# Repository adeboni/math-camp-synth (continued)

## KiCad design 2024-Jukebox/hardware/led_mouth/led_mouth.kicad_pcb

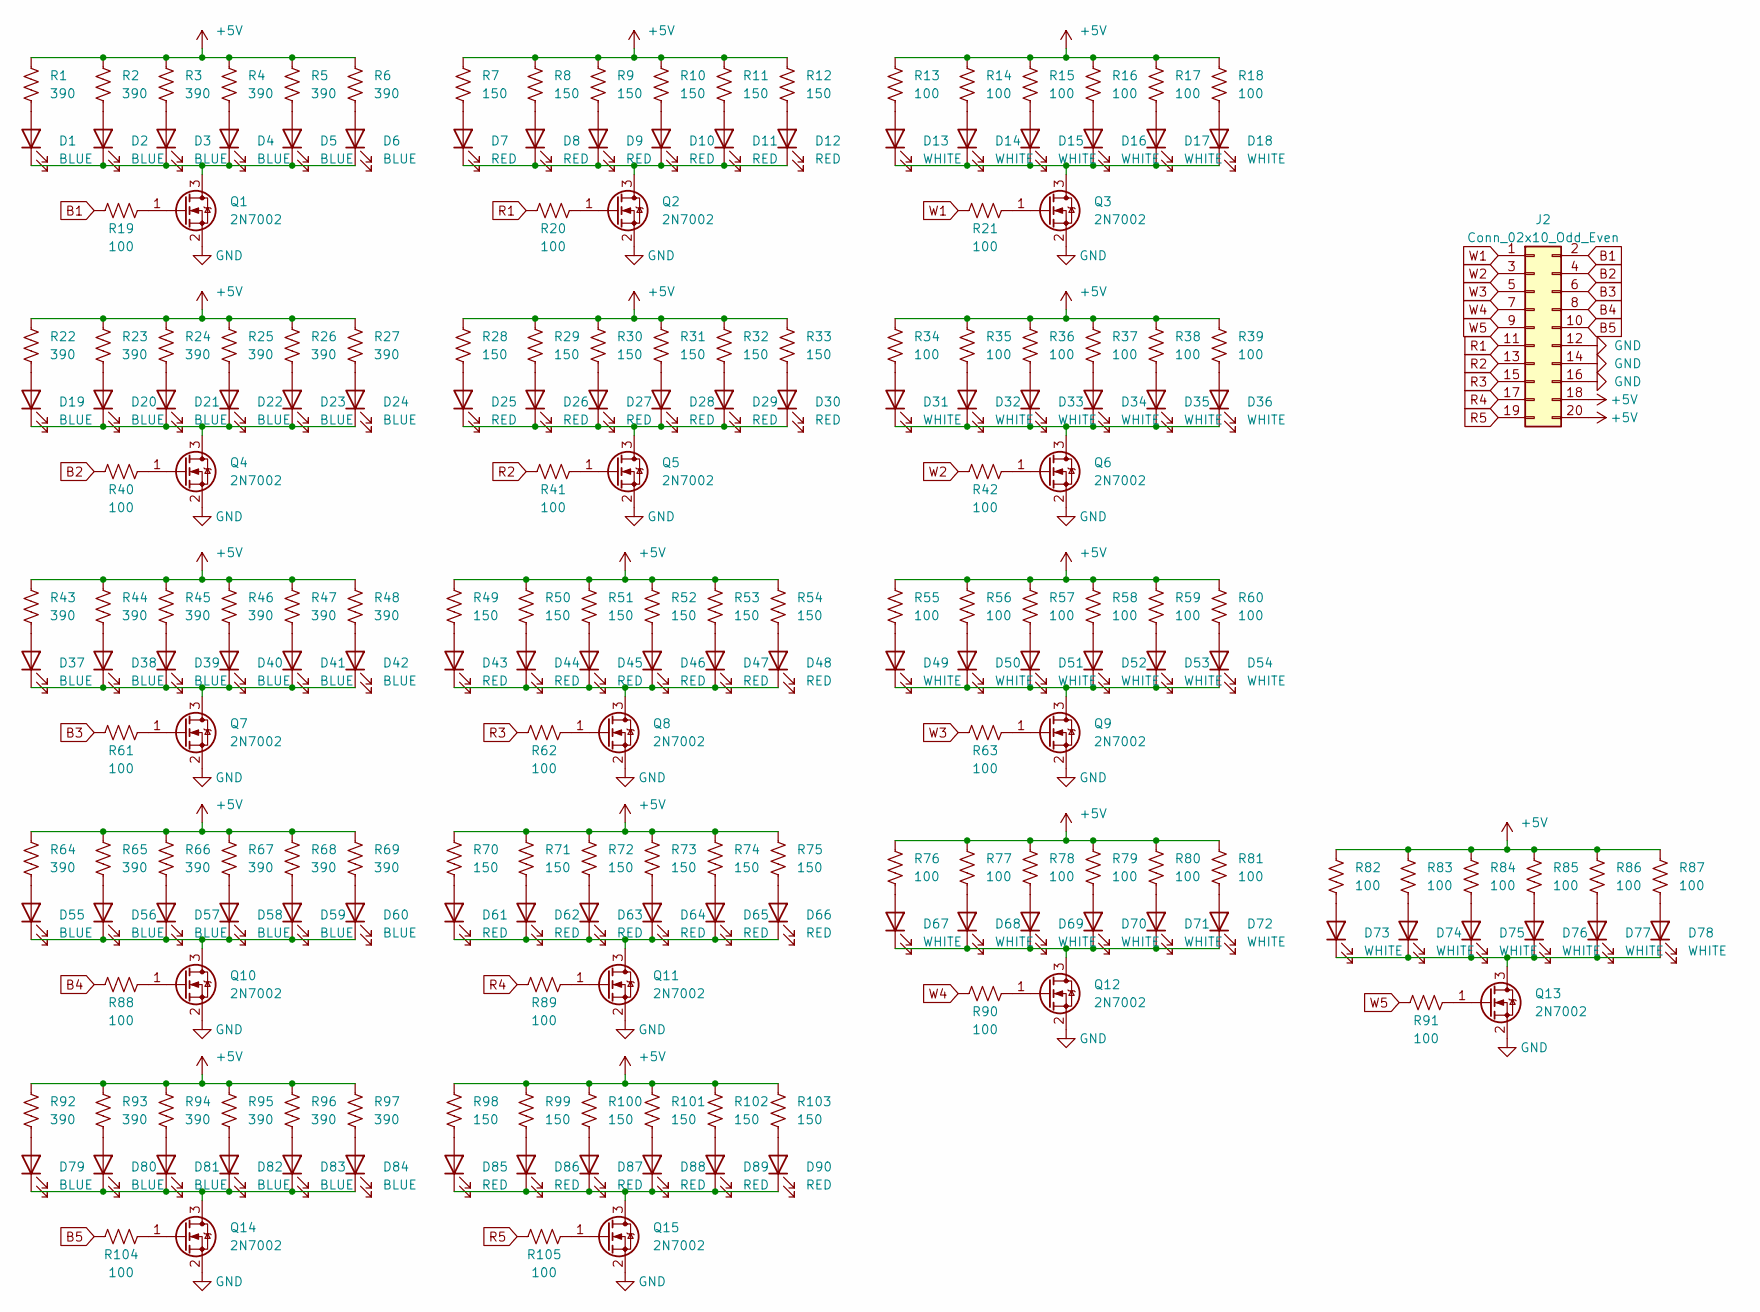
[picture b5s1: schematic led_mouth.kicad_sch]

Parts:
D1, D2, D3, D4, D5, D6, D19, D20, D21, D22, D23, D24, D37, D38, D39, D40, D41, D42, D55, D56, D57, D58, D59, D60, D79, D80, D81, D82, D83, D84: BLUE; LED_0603_1608Metric
D7, D8, D9, D10, D11, D12, D25, D26, D27, D28, D29, D30, D43, D44, D45, D46, D47, D48, D61, D62, D63, D64, D65, D66, D85, D86, D87, D88, D89, D90: RED; LED_0603_1608Metric
D13, D14, D15, D16, D17, D18, D31, D32, D33, D34, D35, D36, D49, D50, D51, D52, D53, D54, D67, D68, D69, D70, D71, D72, D73, D74, D75, D76, D77, D78: WHITE; LED_0603_1608Metric
J2: Conn_02x10_Odd_Even; IDC-Header_2x10_P2.54mm_Vertical_SMD
Q1, Q2, Q3, Q4, Q5, Q6, Q7, Q8, Q9, Q10, Q11, Q12, Q13, Q14, Q15: 2N7002; SOT-23
R1, R2, R3, R4, R5, R6, R22, R23, R24, R25, R26, R27, R43, R44, R45, R46, R47, R48, R64, R65, R66, R67, R68, R69, R92, R93, R94, R95, R96, R97: 390; R_0603_1608Metric
R7, R8, R9, R10, R11, R12, R28, R29, R30, R31, R32, R33, R49, R50, R51, R52, R53, R54, R70, R71, R72, R73, R74, R75, R98, R99, R100, R101, R102, R103: 150; R_0603_1608Metric
R13, R14, R15, R16, R17, R18, R19, R20, R21, R34, R35, R36, R37, R38, R39, R40, R41, R42, R55, R56, R57, R58, R59, R60, R61, R62, R63, R76, R77, R78, R79, R80, R81, R82, R83, R84, R85, R86, R87, R88, R89, R90, R91, R104, R105: 100; R_0603_1608Metric

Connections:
+5V: J2.18, J2.20, R1.2, R2.2, R3.2, R4.2, R5.2, R6.2, R7.2, R8.2, R9.2, R10.2, R11.2, R12.2, R13.2, R14.2, R15.2, R16.2, R17.2, R18.2, R22.2, R23.2, R24.2, R25.2, R26.2, R27.2, R28.2, R29.2, R30.2, R31.2, R32.2, R33.2, R34.2, R35.2, R36.2, R37.2, R38.2, R39.2, R43.2, R44.2, R45.2, R46.2, R47.2, R48.2, R49.2, R50.2, R51.2, R52.2, R53.2, R54.2, R55.2, R56.2, R57.2, R58.2, R59.2, R60.2, R64.2, R65.2, R66.2, R67.2, R68.2, R69.2, R70.2, R71.2, R72.2, R73.2, R74.2, R75.2, R76.2, R77.2, R78.2, R79.2, R80.2, R81.2, R82.2, R83.2, R84.2, R85.2, R86.2, R87.2, R92.2, R93.2, R94.2, R95.2, R96.2, R97.2, R98.2, R99.2, R100.2, R101.2, R102.2, R103.2
B1: J2.2, R19.1
B2: J2.4, R40.1
B3: J2.6, R61.1
B4: J2.8, R88.1
B5: J2.10, R104.1
GND: J2.12, J2.14, J2.16, Q1.2 (S), Q2.2 (S), Q3.2 (S), Q4.2 (S), Q5.2 (S), Q6.2 (S), Q7.2 (S), Q8.2 (S), Q9.2 (S), Q10.2 (S), Q11.2 (S), Q12.2 (S), Q13.2 (S), Q14.2 (S), Q15.2 (S)
unnamed: D1.2 (A), R1.1
unnamed: D1.1 (K), D2.1 (K), D3.1 (K), D4.1 (K), D5.1 (K), D6.1 (K), Q1.3 (D)
unnamed: D2.2 (A), R2.1
unnamed: D3.2 (A), R3.1
unnamed: D4.2 (A), R4.1
unnamed: D5.2 (A), R5.1
unnamed: D6.2 (A), R6.1
unnamed: D7.2 (A), R7.1
unnamed: D8.2 (A), R8.1
unnamed: D9.2 (A), R9.1
unnamed: D10.2 (A), R10.1
unnamed: D7.1 (K), D8.1 (K), D9.1 (K), D10.1 (K), D11.1 (K), D12.1 (K), Q2.3 (D)
unnamed: D11.2 (A), R11.1
unnamed: D12.2 (A), R12.1
unnamed: D13.2 (A), R13.1
unnamed: D13.1 (K), D14.1 (K), D15.1 (K), D16.1 (K), D17.1 (K), D18.1 (K), Q3.3 (D)
unnamed: D14.2 (A), R14.1
unnamed: D15.2 (A), R15.1
unnamed: D16.2 (A), R16.1
unnamed: D17.2 (A), R17.1
unnamed: D18.2 (A), R18.1
unnamed: D19.2 (A), R22.1
unnamed: D19.1 (K), D20.1 (K), D21.1 (K), D22.1 (K), D23.1 (K), D24.1 (K), Q4.3 (D)
unnamed: D20.2 (A), R23.1
unnamed: D21.2 (A), R24.1
unnamed: D22.2 (A), R25.1
unnamed: D23.2 (A), R26.1
unnamed: D24.2 (A), R27.1
unnamed: D25.2 (A), R28.1
unnamed: D25.1 (K), D26.1 (K), D27.1 (K), D28.1 (K), D29.1 (K), D30.1 (K), Q5.3 (D)
unnamed: D26.2 (A), R29.1
unnamed: D27.2 (A), R30.1
unnamed: D28.2 (A), R31.1
unnamed: D29.2 (A), R32.1
unnamed: D30.2 (A), R33.1
unnamed: D31.2 (A), R34.1
unnamed: D31.1 (K), D32.1 (K), D33.1 (K), D34.1 (K), D35.1 (K), D36.1 (K), Q6.3 (D)
unnamed: D32.2 (A), R35.1
unnamed: D33.2 (A), R36.1
unnamed: D34.2 (A), R37.1
unnamed: D35.2 (A), R38.1
unnamed: D36.2 (A), R39.1
unnamed: D37.2 (A), R43.1
unnamed: D37.1 (K), D38.1 (K), D39.1 (K), D40.1 (K), D41.1 (K), D42.1 (K), Q7.3 (D)
unnamed: D38.2 (A), R44.1
unnamed: D39.2 (A), R45.1
unnamed: D40.2 (A), R46.1
unnamed: D41.2 (A), R47.1
unnamed: D42.2 (A), R48.1
unnamed: D43.2 (A), R49.1
unnamed: D43.1 (K), D44.1 (K), D45.1 (K), D46.1 (K), D47.1 (K), D48.1 (K), Q8.3 (D)
unnamed: D44.2 (A), R50.1
unnamed: D45.2 (A), R51.1
unnamed: D46.2 (A), R52.1
unnamed: D47.2 (A), R53.1
unnamed: D48.2 (A), R54.1
unnamed: D49.2 (A), R55.1
unnamed: D49.1 (K), D50.1 (K), D51.1 (K), D52.1 (K), D53.1 (K), D54.1 (K), Q9.3 (D)
unnamed: D50.2 (A), R56.1
unnamed: D51.2 (A), R57.1
unnamed: D52.2 (A), R58.1
unnamed: D53.2 (A), R59.1
unnamed: D54.2 (A), R60.1
unnamed: D55.2 (A), R64.1
unnamed: D55.1 (K), D56.1 (K), D57.1 (K), D58.1 (K), D59.1 (K), D60.1 (K), Q10.3 (D)
unnamed: D56.2 (A), R65.1
unnamed: D57.2 (A), R66.1
unnamed: D58.2 (A), R67.1
unnamed: D59.2 (A), R68.1
unnamed: D60.2 (A), R69.1
unnamed: D61.2 (A), R70.1
unnamed: D61.1 (K), D62.1 (K), D63.1 (K), D64.1 (K), D65.1 (K), D66.1 (K), Q11.3 (D)
unnamed: D62.2 (A), R71.1
unnamed: D63.2 (A), R72.1
unnamed: D64.2 (A), R73.1
unnamed: D65.2 (A), R74.1
unnamed: D66.2 (A), R75.1
unnamed: D67.2 (A), R76.1
unnamed: D67.1 (K), D68.1 (K), D69.1 (K), D70.1 (K), D71.1 (K), D72.1 (K), Q12.3 (D)
unnamed: D68.2 (A), R77.1
unnamed: D69.2 (A), R78.1
unnamed: D70.2 (A), R79.1
unnamed: D71.2 (A), R80.1
unnamed: D72.2 (A), R81.1
unnamed: D73.2 (A), R82.1
unnamed: D73.1 (K), D74.1 (K), D75.1 (K), D76.1 (K), D77.1 (K), D78.1 (K), Q13.3 (D)
unnamed: D74.2 (A), R83.1
unnamed: D75.2 (A), R84.1
unnamed: D76.2 (A), R85.1
unnamed: D77.2 (A), R86.1
unnamed: D78.2 (A), R87.1
unnamed: D79.2 (A), R92.1
unnamed: D79.1 (K), D80.1 (K), D81.1 (K), D82.1 (K), D83.1 (K), D84.1 (K), Q14.3 (D)
unnamed: D80.2 (A), R93.1
unnamed: D81.2 (A), R94.1
unnamed: D82.2 (A), R95.1
unnamed: D83.2 (A), R96.1
unnamed: D84.2 (A), R97.1
unnamed: D85.2 (A), R98.1
unnamed: D85.1 (K), D86.1 (K), D87.1 (K), D88.1 (K), D89.1 (K), D90.1 (K), Q15.3 (D)
unnamed: D86.2 (A), R99.1
unnamed: D87.2 (A), R100.1
unnamed: D88.2 (A), R101.1
unnamed: D89.2 (A), R102.1
unnamed: D90.2 (A), R103.1
unnamed: Q1.1 (G), R19.2
unnamed: Q2.1 (G), R20.2
unnamed: Q3.1 (G), R21.2
unnamed: Q4.1 (G), R40.2
unnamed: Q5.1 (G), R41.2
unnamed: Q6.1 (G), R42.2
unnamed: Q7.1 (G), R61.2
unnamed: Q8.1 (G), R62.2
unnamed: Q9.1 (G), R63.2
unnamed: Q10.1 (G), R88.2
unnamed: Q11.1 (G), R89.2
unnamed: Q12.1 (G), R90.2
unnamed: Q13.1 (G), R91.2
unnamed: Q14.1 (G), R104.2
unnamed: Q15.1 (G), R105.2
R1: J2.11, R20.1
R2: J2.13, R41.1
R3: J2.15, R62.1
R4: J2.17, R89.1
R5: J2.19, R105.1
W1: J2.1, R21.1
W2: J2.3, R42.1
W3: J2.5, R63.1
W4: J2.7, R90.1
W5: J2.9, R91.1

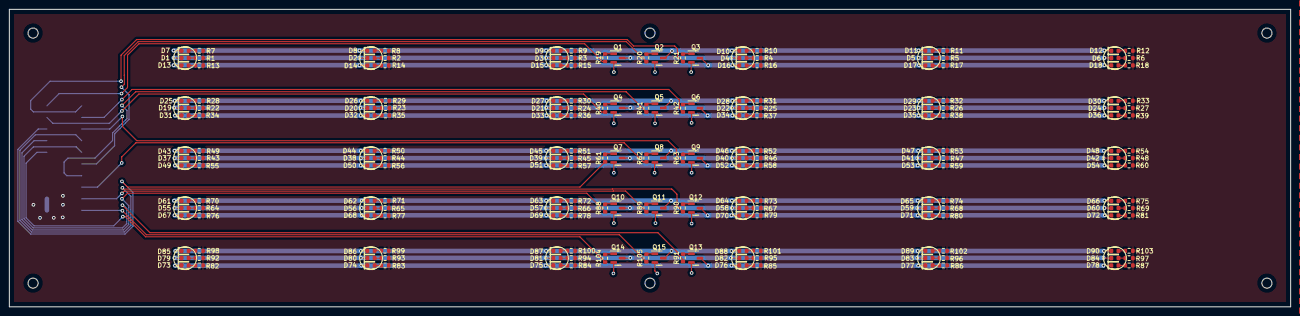
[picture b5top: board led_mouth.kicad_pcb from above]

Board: 2 copper layers, 280.0 x 65.0 mm, 211 parts (1 on the bottom side), 137 nets.

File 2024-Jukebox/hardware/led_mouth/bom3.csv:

Comment,Designator,Footprint,LCSC Part #
390,"R1,R48,R95,R65,R22,R64,R68,R4,R25,R3,R24,R96,R46,R26,R94,R66,R2,R5,R45,R47,R43,R6,R23,R93,R92,R67,R69,R97,R27,R44",R_0603_1608Metric,C23151
150,"R99,R52,R70,R102,R9,R29,R72,R98,R50,R74,R103,R8,R75,R12,R73,R11,R53,R101,R30,R71,R28,R51,R100,R32,R49,R54,R33,R31,R10,R7",R_0603_1608Metric,C22808
RED,"D9,D90,D86,D87,D45,D88,D10,D63,D43,D48,D65,D64,D30,D7,D44,D26,D47,D11,D61,D27,D29,D12,D46,D25,D62,D28,D89,D85,D66,D8",LED_0603_1608Metric,C2286
100,"R35,R62,R63,R42,R34,R83,R80,R89,R19,R39,R40,R14,R38,R78,R105,R86,R84,R61,R15,R37,R87,R91,R58,R76,R88,R57,R104,R82,R18,R77,R41,R16,R60,R20,R17,R55,R79,R85,R13,R36,R56,R21,R90,R59,R81",R_0603_1608Metric,C22775
2N7002,"Q7,Q6,Q9,Q8,Q3,Q5,Q14,Q1,Q4,Q12,Q11,Q15,Q10,Q13,Q2",SOT-23,C8545
WHITE,"D76,D13,D53,D70,D54,D52,D49,D33,D69,D77,D31,D32,D15,D68,D34,D78,D36,D74,D17,D18,D51,D67,D16,D73,D71,D50,D75,D72,D14,D35",LED_0603_1608Metric,C2290
BLUE,"D80,D81,D55,D56,D57,D84,D2,D37,D79,D22,D5,D4,D82,D21,D3,D1,D6,D38,D58,D24,D19,D60,D41,D23,D20,D83,D40,D59,D42,D39",LED_0603_1608Metric,C72041

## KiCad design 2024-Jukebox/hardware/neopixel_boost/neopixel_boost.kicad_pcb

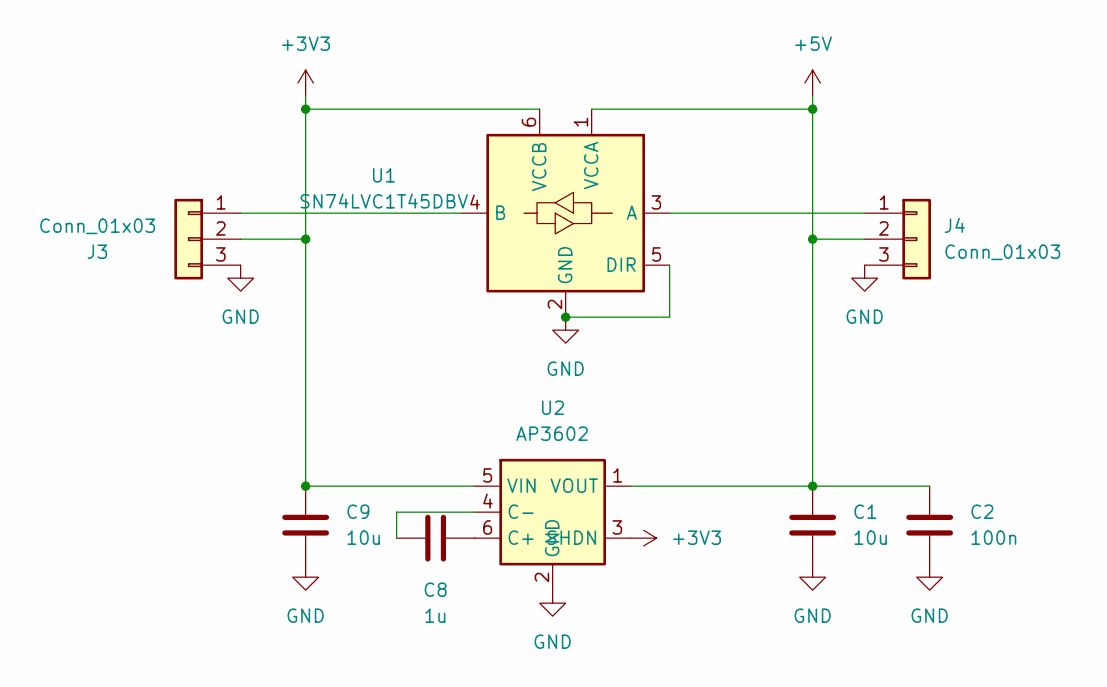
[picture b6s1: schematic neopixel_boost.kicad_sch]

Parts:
C1, C9: 10u; C_0402_1005Metric
C2: 100n; C_0402_1005Metric
C8: 1u; C_0402_1005Metric
J3, J4: Conn_01x03; PinHeader_1x03_P2.54mm_Vertical
U1: SN74LVC1T45DBV; SOT-23-6
U2: AP3602; SOT-23-6

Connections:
+3V3: C9.1, J3.2, U1.6 (VCCB), U2.3 (SHDN), U2.5 (VIN)
+5V: C1.1, C2.1, J4.2, U1.1 (VCCA), U2.1 (VOUT)
GND: C1.2, C2.2, C9.2, J3.3, J4.3, U1.2 (GND), U1.5 (DIR), U2.2 (GND)
unnamed: J3.1, U1.4 (B)
unnamed: J4.1, U1.3 (A)
unnamed: C8.2, U2.6 (C+)
unnamed: C8.1, U2.4 (C-)

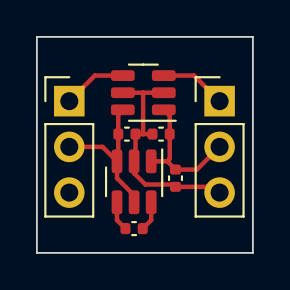
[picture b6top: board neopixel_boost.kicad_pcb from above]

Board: 2 copper layers, 12.0 x 12.0 mm, 8 parts (0 on the bottom side), 7 nets.

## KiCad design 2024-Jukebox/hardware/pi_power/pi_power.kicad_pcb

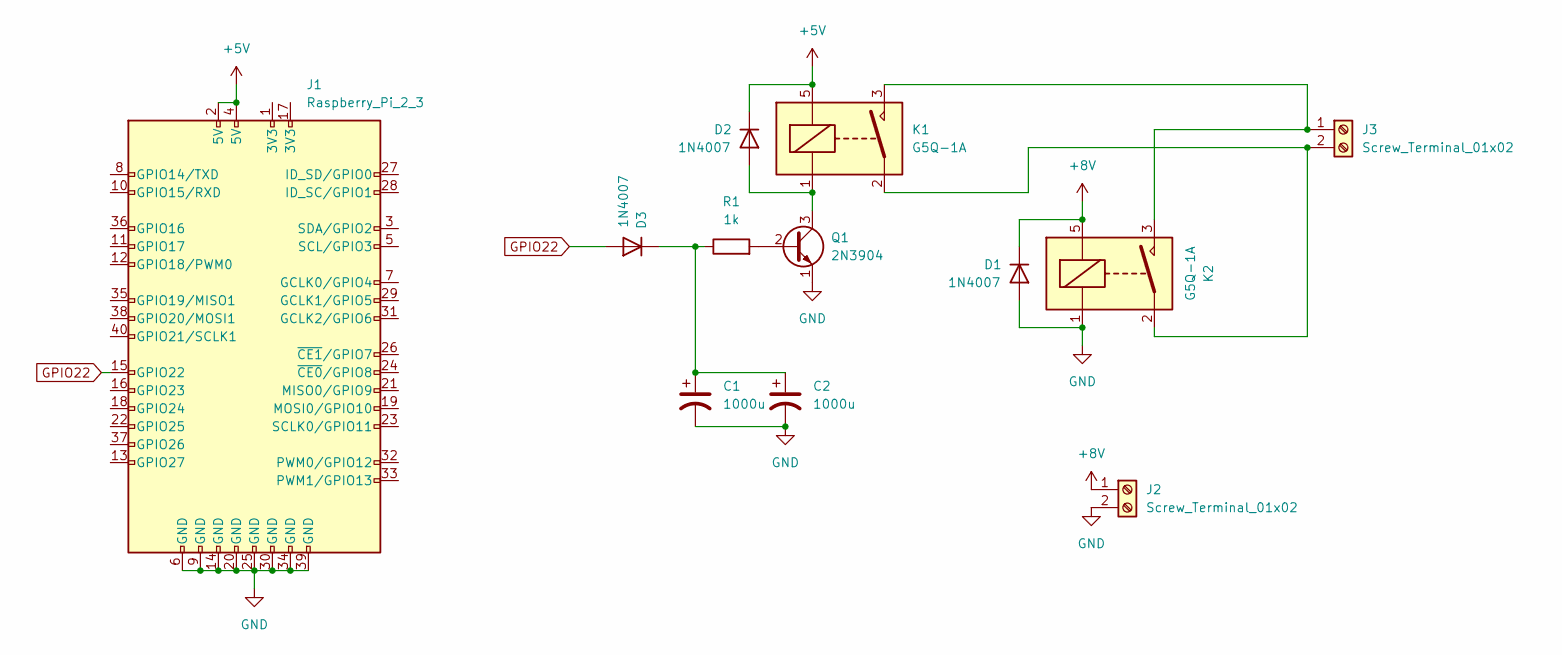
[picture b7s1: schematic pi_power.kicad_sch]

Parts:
C1, C2: 1000u; CP_Radial_D8.0mm_P3.50mm
D1, D2, D3: 1N4007; D_DO-41_SOD81_P10.16mm_Horizontal
J1: Raspberry_Pi_2_3; PinSocket_2x20_P2.54mm_Vertical
J2, J3: Screw_Terminal_01x02; TerminalBlock_Phoenix_MKDS-1,5-2-5.08_1x02_P5.08mm_Horizont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
K1, K2: G5Q-1A; Relay_SPST_Omron-G5Q-1A
Q1: 2N3904; TO-92_Inline
R1: 1k; R_Axial_DIN0207_L6.3mm_D2.5mm_P7.62mm_Horizontal

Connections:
+5V: D2.1 (K), J1.2 (5V), J1.4 (5V), K1.5
+8V: D1.1 (K), J2.1, K2.5
GND: C1.2, C2.2, D1.2 (A), J1.6 (GND), J1.9 (GND), J1.14 (GND), J1.20 (GND), J1.25 (GND), J1.30 (GND), J1.34 (GND), J1.39 (GND), J2.2, K2.1, Q1.1 (E)
GPIO22: D3.2 (A), J1.15 (GPIO22)
unnamed: D2.2 (A), K1.1, Q1.3 (C)
unnamed: C1.1, C2.1, D3.1 (K), R1.1
unnamed: J3.1, K1.3, K2.3
unnamed: J3.2, K1.2, K2.2
unnamed: Q1.2 (B), R1.2

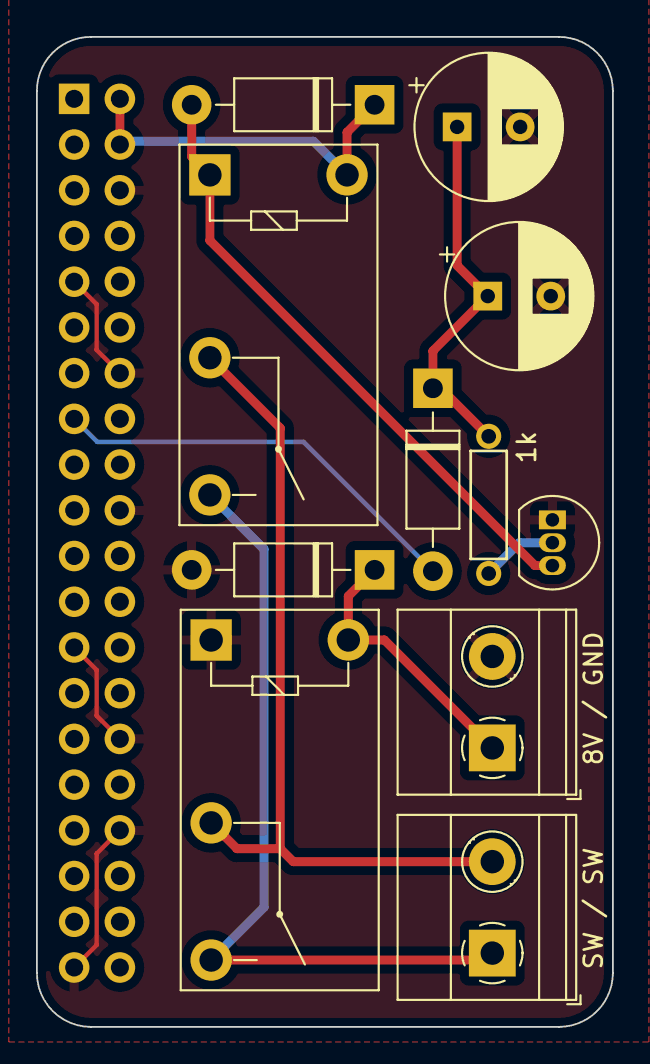
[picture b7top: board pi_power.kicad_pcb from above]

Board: 2 copper layers, 32.0 x 55.0 mm, 12 parts (1 on the bottom side), 9 nets.

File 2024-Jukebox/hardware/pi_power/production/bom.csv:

Designator,Footprint,Quantity,Value,LCSC Part #
"C1, C2",CP_Radial_D8.0mm_P3.50mm,2,1000u,
"D1, D2, D3",D_DO-41_SOD81_P10.16mm_Horizontal,3,1N4007,
J1,PinSocket_2x20_P2.54mm_Vertical,1,Raspberry_Pi_2_3,
"J2, J3","TerminalBlock_Phoenix_MKDS-1,5-2-5.08_1x02_P5.08mm_Horizontal",2,Screw_Terminal_01x02,
"K1, K2",Relay_SPST_Omron-G5Q-1A,2,G5Q-1A,
Q1,TO-92_Inline,1,2N3904,
R1,R_Axial_DIN0207_L6.3mm_D2.5mm_P7.62mm_Horizontal,1,1k,
